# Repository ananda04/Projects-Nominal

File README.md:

# Projects-Nominal

A collection of applications, hardware designs, and automation tools built for the Nominal Connect ecosystem.

## Projects Overview

### `ciRACK`
Configurations, soft-control utilities, and automation scripts for managing hardware test rack infrastructure and VISA-connected instrumentation.

### `connectBAMBU`
Nominal Connect application for integrating Bambu Lab 3D printers, processing G-code print instructions, and streaming telemetry to Nominal.

### `connectModule`
Custom hardware design and embedded setup for a standalone RS-232 to Ethernet adapter board running Connect Engine to enable no-code test rack instrument interfacing.

### `gem5-connect`
Nominal Connect runner and data processing pipeline for executing gem5 Garnet Network-on-Chip (NoC) synthetic traffic sweeps via Docker and streaming post-evaluation telemetry to Nominal Core.

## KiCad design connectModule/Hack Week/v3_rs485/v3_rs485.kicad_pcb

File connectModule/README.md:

# Connect Serial-to-Ethernet Node

Standalone hardware adapter that bridges legacy test rack equipment (RS-232 / SCPI) to the Nominal Connect ecosystem via Ethernet. By running an embedded instance of Connect Engine directly on the node, it offloads driver execution and enables a no-code setup for test instrumentation.

## Implementation & Demo

The final implementation was scaled to run on a Raspberry Pi Compute platform running Linux. This preserved full Rust standard library (`std`) support, dynamic driver loading, and rapid SSH deployment without requiring a re-architecture of Connect Engine.

* Demo Video: https://youtu.be/hmSoeRTddCs?si=SxnHFOz03OIot3RP

## Key Hardware Specifications

* Power Input: 9–30V DC via 2-pin screw terminals (Buck converter rated up to 60V for potential future PoE support).
* Serial Interface: Male DB9 connector supporting RS-232 levels via MAX3232 transceiver.
* Network Interface: 100 Mbps RJ45 Ethernet using a W5500 SPI controller.
* Compute & Storage: Raspberry Pi Zero 2 W (Quad-core ARM Cortex-A53) with MicroSD for local OS and logging.

## Circuit Summary

* Power Subsystem: 9–30V DC input -> 4-60V Buck Converter (5V output) -> AMS1117-3.3 LDO (3.3V rail for level shifters and PHY).
* Serial Communication: DB9 RS-232 (+/-15V) converted to 3.3V logic via MAX3232 transceiver to Pi UART.
* Network Subsystem: W5500 IC offloads TCP/IP processing over SPI to the Pi, outputting via an integrated magnetics RJ45 jack.

## Software & Workflow

1. Stack: Raspberry Pi OS (Linux) running Connect Engine (compiled in Rust) integrated with Nominal Data Link for telemetry and commanding.
2. Setup: Connect DB9 to target instrument, attach Ethernet, and apply 9–30V DC power.
3. Usage: Locate node in Nominal Connect UI, configure instrument protocol, and control hardware without custom code.

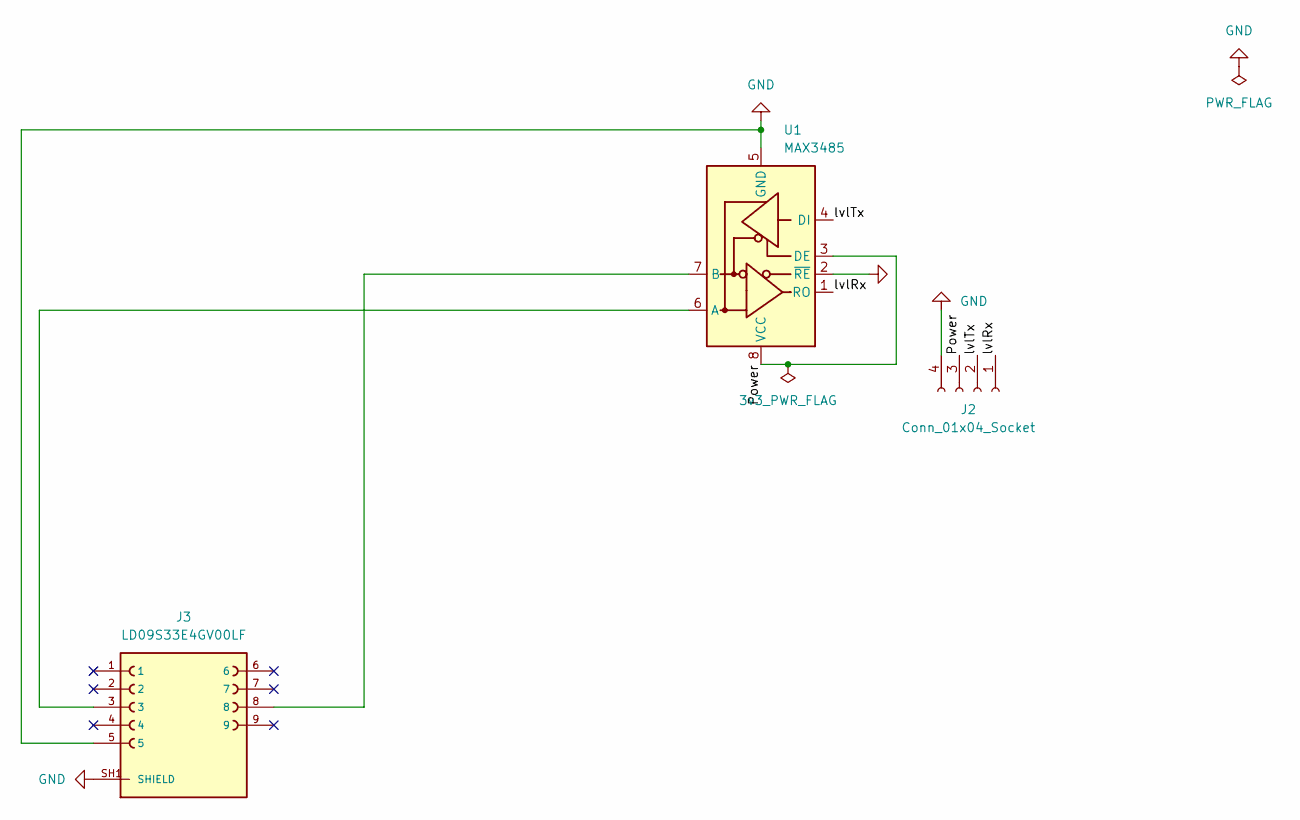
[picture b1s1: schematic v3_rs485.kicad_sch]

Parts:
J2: Conn_01x04_Socket; PinSocket_1x04_P2.54mm_Vertical
J3: LD09S33E4GV00LF; AMPHENOL_LD09S33E4GV00LF; PARTREV B
U1: MAX3485; SOIC-8_3.9x4.9mm_P1.27mm

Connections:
/Power: J2.3, U1.3 (DE), U1.8 (VCC)
/lvlRx: J2.1, U1.1 (RO)
/lvlTx: J2.2, U1.4 (DI)
GND: J2.4, J3.5, J3.SH1 (SHIELD), J3.SH2 (SHIELD), U1.2 (~RE), U1.5 (GND)
unnamed: J3.3, U1.6 (A)
unnamed: J3.8, U1.7 (B)

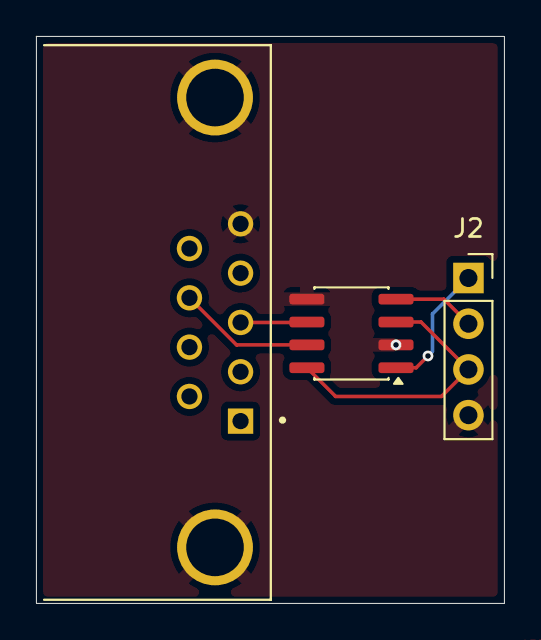
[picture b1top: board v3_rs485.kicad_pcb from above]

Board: 2 copper layers, 26.0 x 31.5 mm, 3 parts (0 on the bottom side), 6 nets.

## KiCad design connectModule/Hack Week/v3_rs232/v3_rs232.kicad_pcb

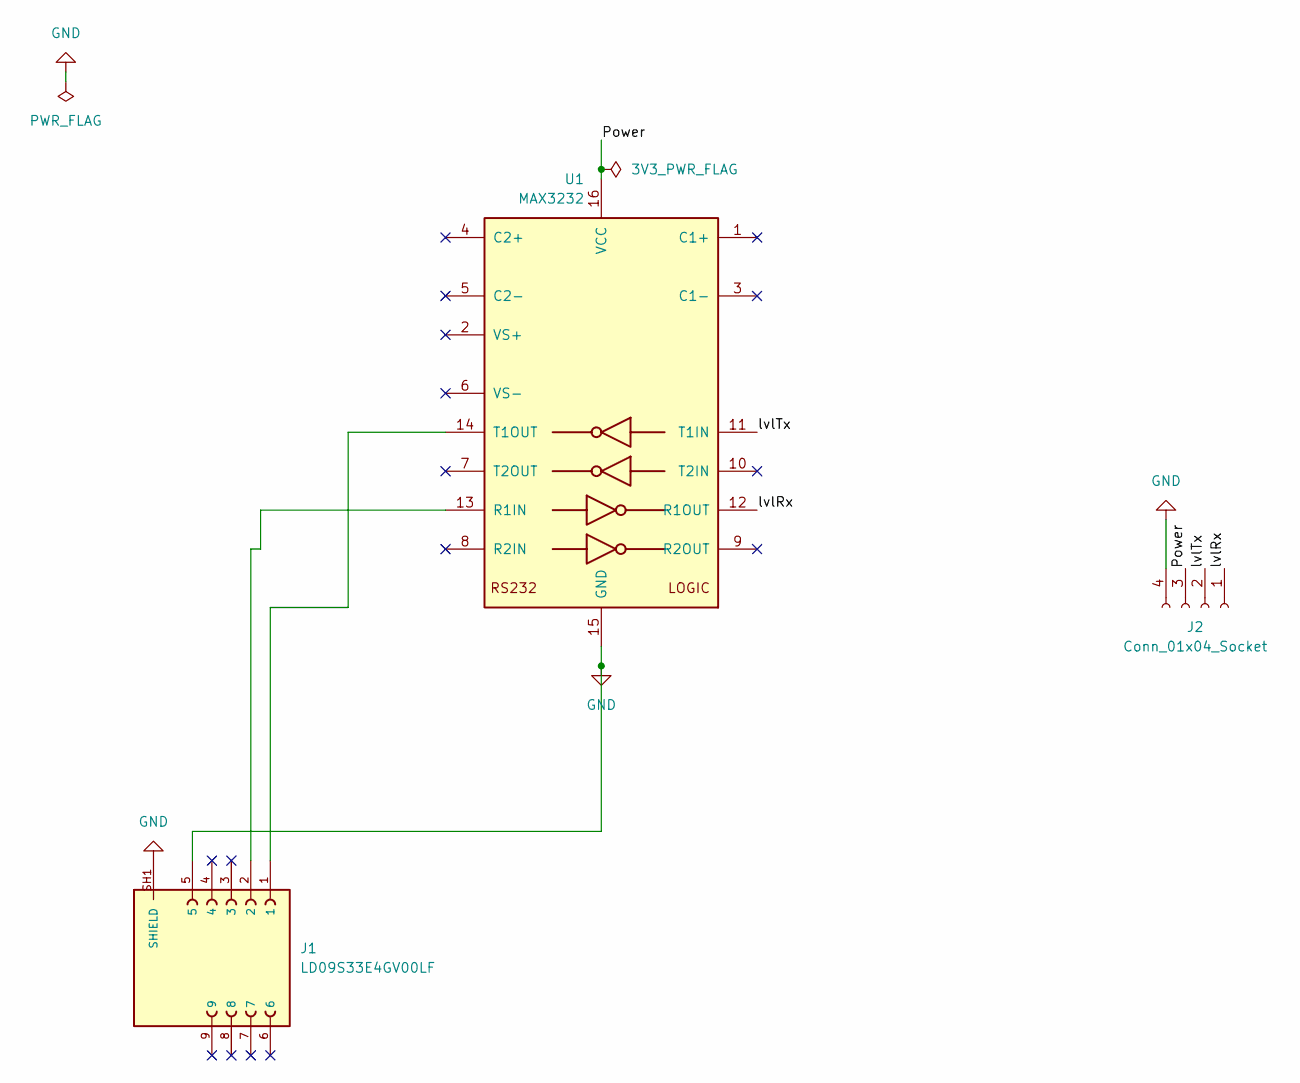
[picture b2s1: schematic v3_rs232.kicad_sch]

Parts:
J1: LD09S33E4GV00LF; AMPHENOL_LD09S33E4GV00LF; PARTREV B
J2: Conn_01x04_Socket; PinSocket_1x04_P2.54mm_Vertical
U1: MAX3232; TSSOP-16_4.4x5mm_P0.65mm

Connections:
/Power: J2.3, U1.16 (VCC)
/lvlRx: J2.1, U1.12 (R1OUT)
/lvlTx: J2.2, U1.11 (T1IN)
GND: J1.5, J1.SH1 (SHIELD), J1.SH2 (SHIELD), J2.4, U1.15 (GND)
unnamed: J1.2, U1.13 (R1IN)
unnamed: J1.1, U1.14 (T1OUT)

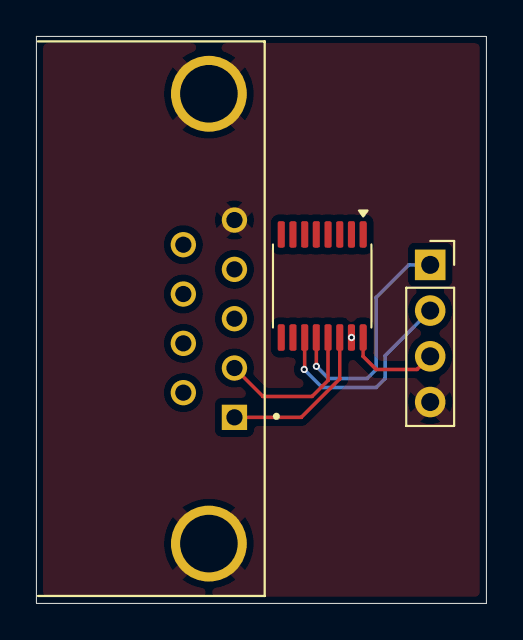
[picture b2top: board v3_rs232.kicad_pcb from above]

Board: 2 copper layers, 25.0 x 31.5 mm, 3 parts (0 on the bottom side), 6 nets.

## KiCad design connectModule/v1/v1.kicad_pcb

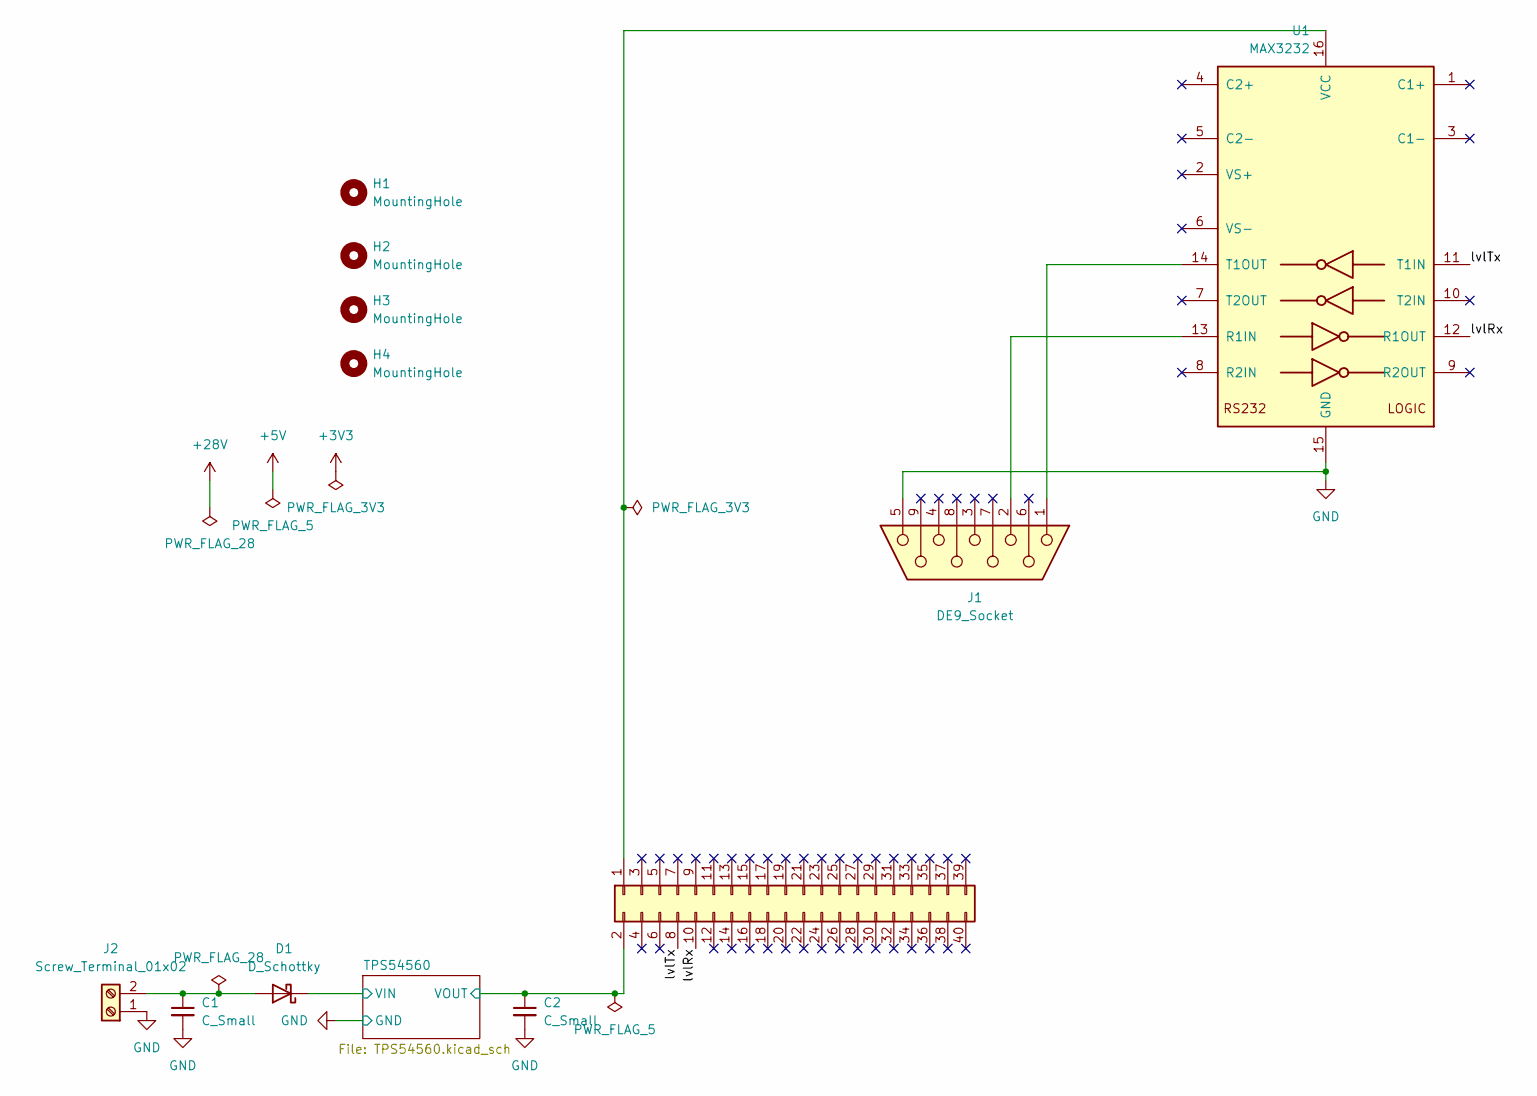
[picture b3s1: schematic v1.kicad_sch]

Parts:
C1, C2: C_Small; C_0402_1005Metric
D1: D_Schottky; D_SMB
H1, H2, H3, H4: MountingHole; MountingHole_2.7mm_M2.5
J1: DE9_Socket; DSUB-9_Socket_EdgeMount_P2.77mm
J2: Screw_Terminal_01x02; TerminalBlock_Phoenix_MKDS-1,5-2_1x02_P5.00mm_Horizontal
J7: Conn_02x20_Odd_Even; PinHeader_2x20_P2.54mm_Vertical
U1: MAX3232; TSSOP-16_4.4x5mm_P0.65mm

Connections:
/TPS54560/VIN: D1.1 (K); also elsewhere on the board
/TPS54560/VOUT: C2.1, J7.2; also elsewhere on the board
/lvlRx: J7.10, U1.12 (R1OUT)
/lvlTx: J7.8, U1.11 (T1IN)
GND: C1.2, C2.2, J1.5, J2.1, U1.15 (GND); also elsewhere on the board
unnamed: C1.1, D1.2 (A), J2.2
unnamed: J7.1, U1.16 (VCC)
unnamed: J1.2, U1.13 (R1IN)
unnamed: J1.1, U1.14 (T1OUT)

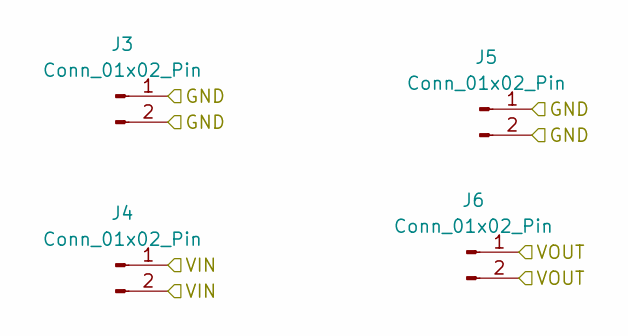
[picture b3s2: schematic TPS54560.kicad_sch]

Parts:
J3, J4, J5, J6: Conn_01x02_Pin; PinHeader_1x02_P2.54mm_Vertical

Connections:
/TPS54560/VIN: J4.1, J4.2; also elsewhere on the board
/TPS54560/VOUT: J6.1, J6.2; also elsewhere on the board
GND: J3.1, J3.2, J5.1, J5.2; also elsewhere on the board

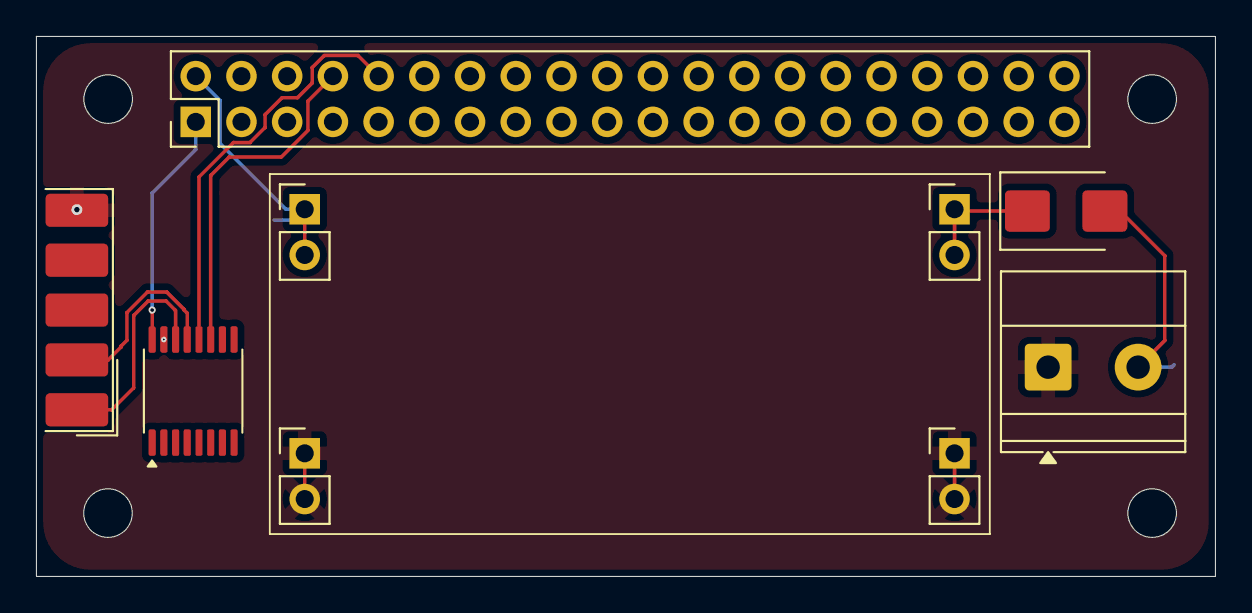
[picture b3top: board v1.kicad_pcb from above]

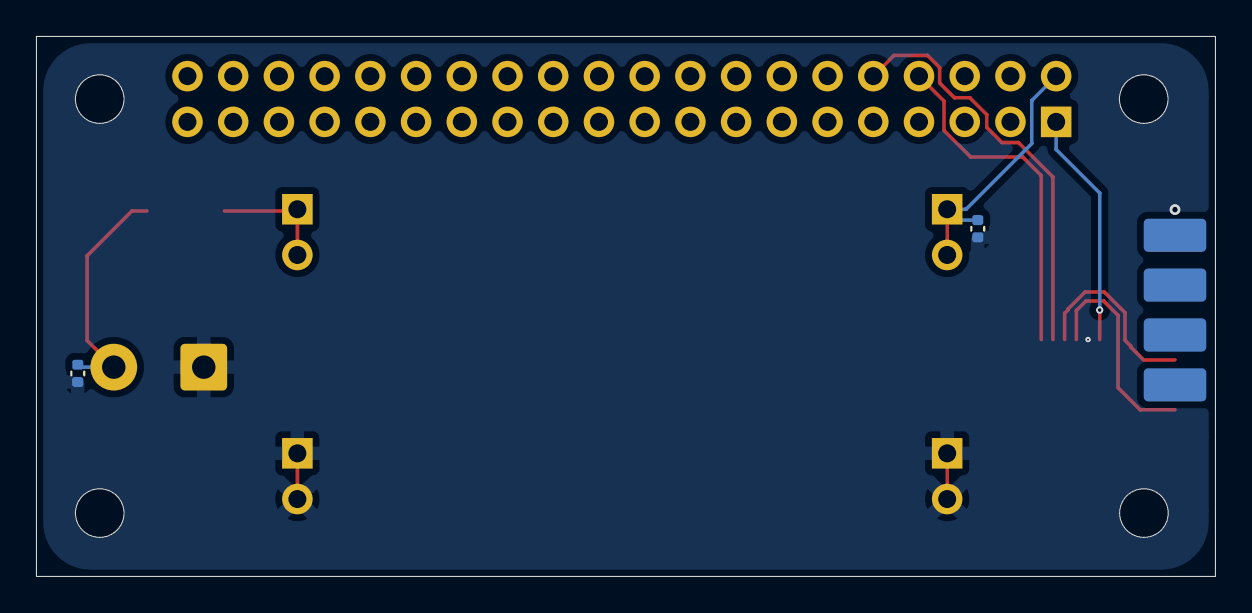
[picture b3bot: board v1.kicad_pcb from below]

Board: 2 copper layers, 65.5 x 30.0 mm, 15 parts (2 on the bottom side), 9 nets.

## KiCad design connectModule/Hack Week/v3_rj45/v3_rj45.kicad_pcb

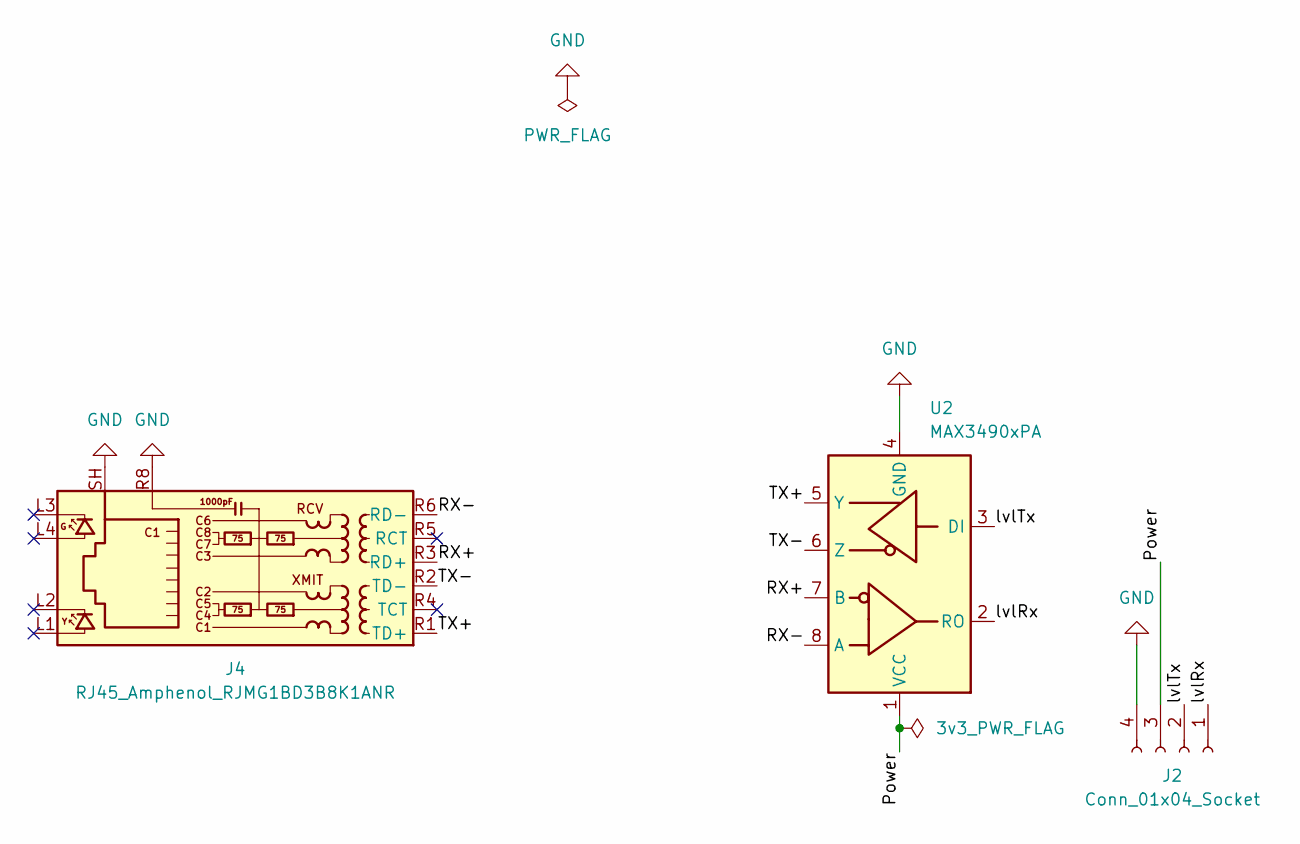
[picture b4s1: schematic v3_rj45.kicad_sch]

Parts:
J2: Conn_01x04_Socket; PinSocket_1x04_P2.54mm_Vertical
J4: RJ45_Amphenol_RJMG1BD3B8K1ANR
U2: MAX3490xPA; DIP-8_W7.62mm

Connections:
/Power: J2.3, U2.1 (VCC)
/RX+: J4.R3 (RD+), U2.7 (B)
/RX-: J4.R6 (RD-), U2.8 (A)
/TX+: J4.R1 (TD+), U2.5 (Y)
/TX-: J4.R2 (TD-), U2.6 (Z)
/lvlRx: J2.1, U2.2 (RO)
/lvlTx: J2.2, U2.3 (DI)
GND: J2.4, J4.R8, J4.SH, U2.4 (GND)

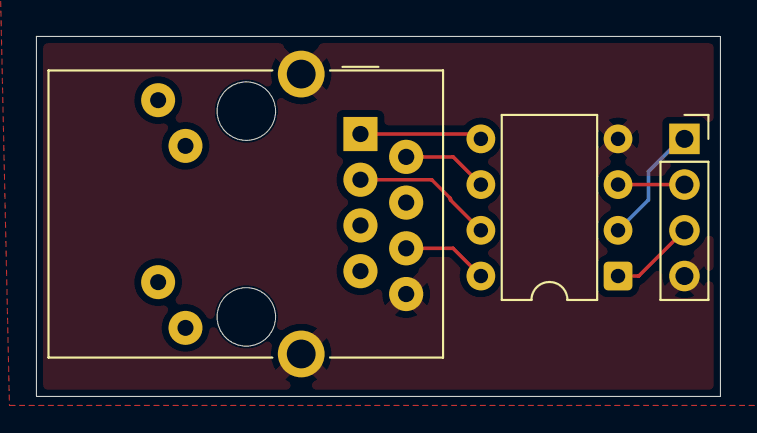
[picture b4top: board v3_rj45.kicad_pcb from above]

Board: 2 copper layers, 38.0 x 20.0 mm, 3 parts (0 on the bottom side), 8 nets.

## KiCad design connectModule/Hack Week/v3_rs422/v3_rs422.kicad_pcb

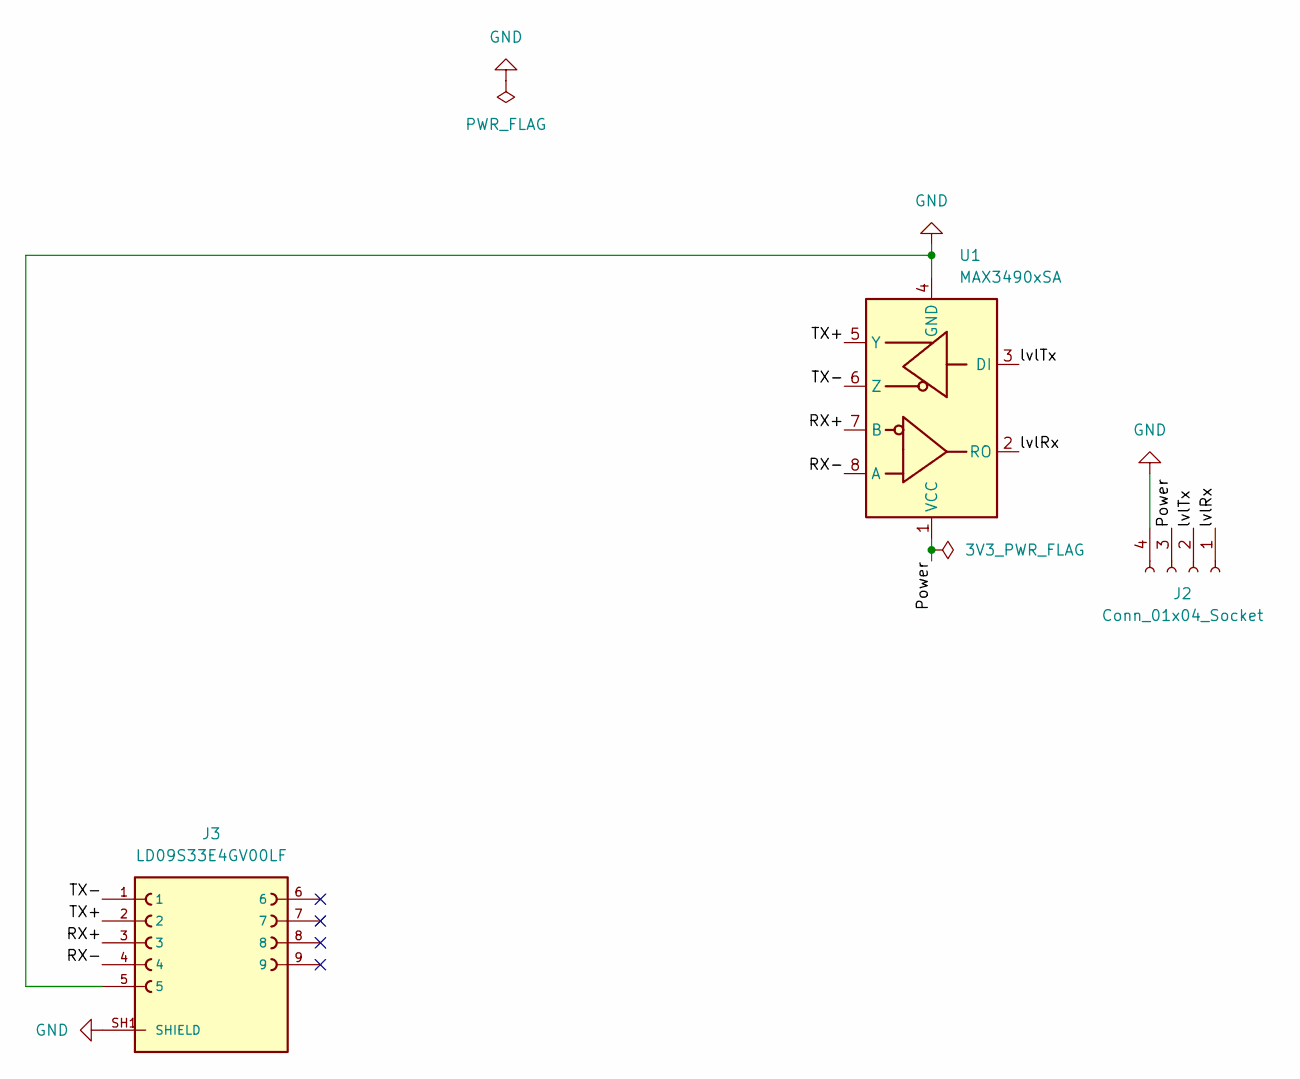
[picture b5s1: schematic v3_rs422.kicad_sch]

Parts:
J2: Conn_01x04_Socket; PinSocket_1x04_P2.54mm_Vertical
J3: LD09S33E4GV00LF; AMPHENOL_LD09S33E4GV00LF; PARTREV B
U1: MAX3490xSA; SOIC-8_3.9x4.9mm_P1.27mm

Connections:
/Power: J2.3, U1.1 (VCC)
/RX+: J3.3, U1.7 (B)
/RX-: J3.4, U1.8 (A)
/TX+: J3.2, U1.5 (Y)
/TX-: J3.1, U1.6 (Z)
/lvlRx: J2.1, U1.2 (RO)
/lvlTx: J2.2, U1.3 (DI)
GND: J2.4, J3.5, J3.SH1 (SHIELD), J3.SH2 (SHIELD), U1.4 (GND)

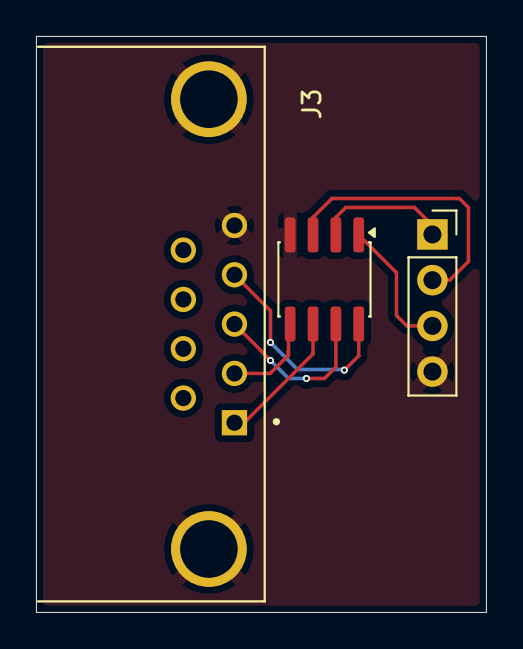
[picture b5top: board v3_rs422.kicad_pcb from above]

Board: 2 copper layers, 25.0 x 32.0 mm, 3 parts (0 on the bottom side), 8 nets.

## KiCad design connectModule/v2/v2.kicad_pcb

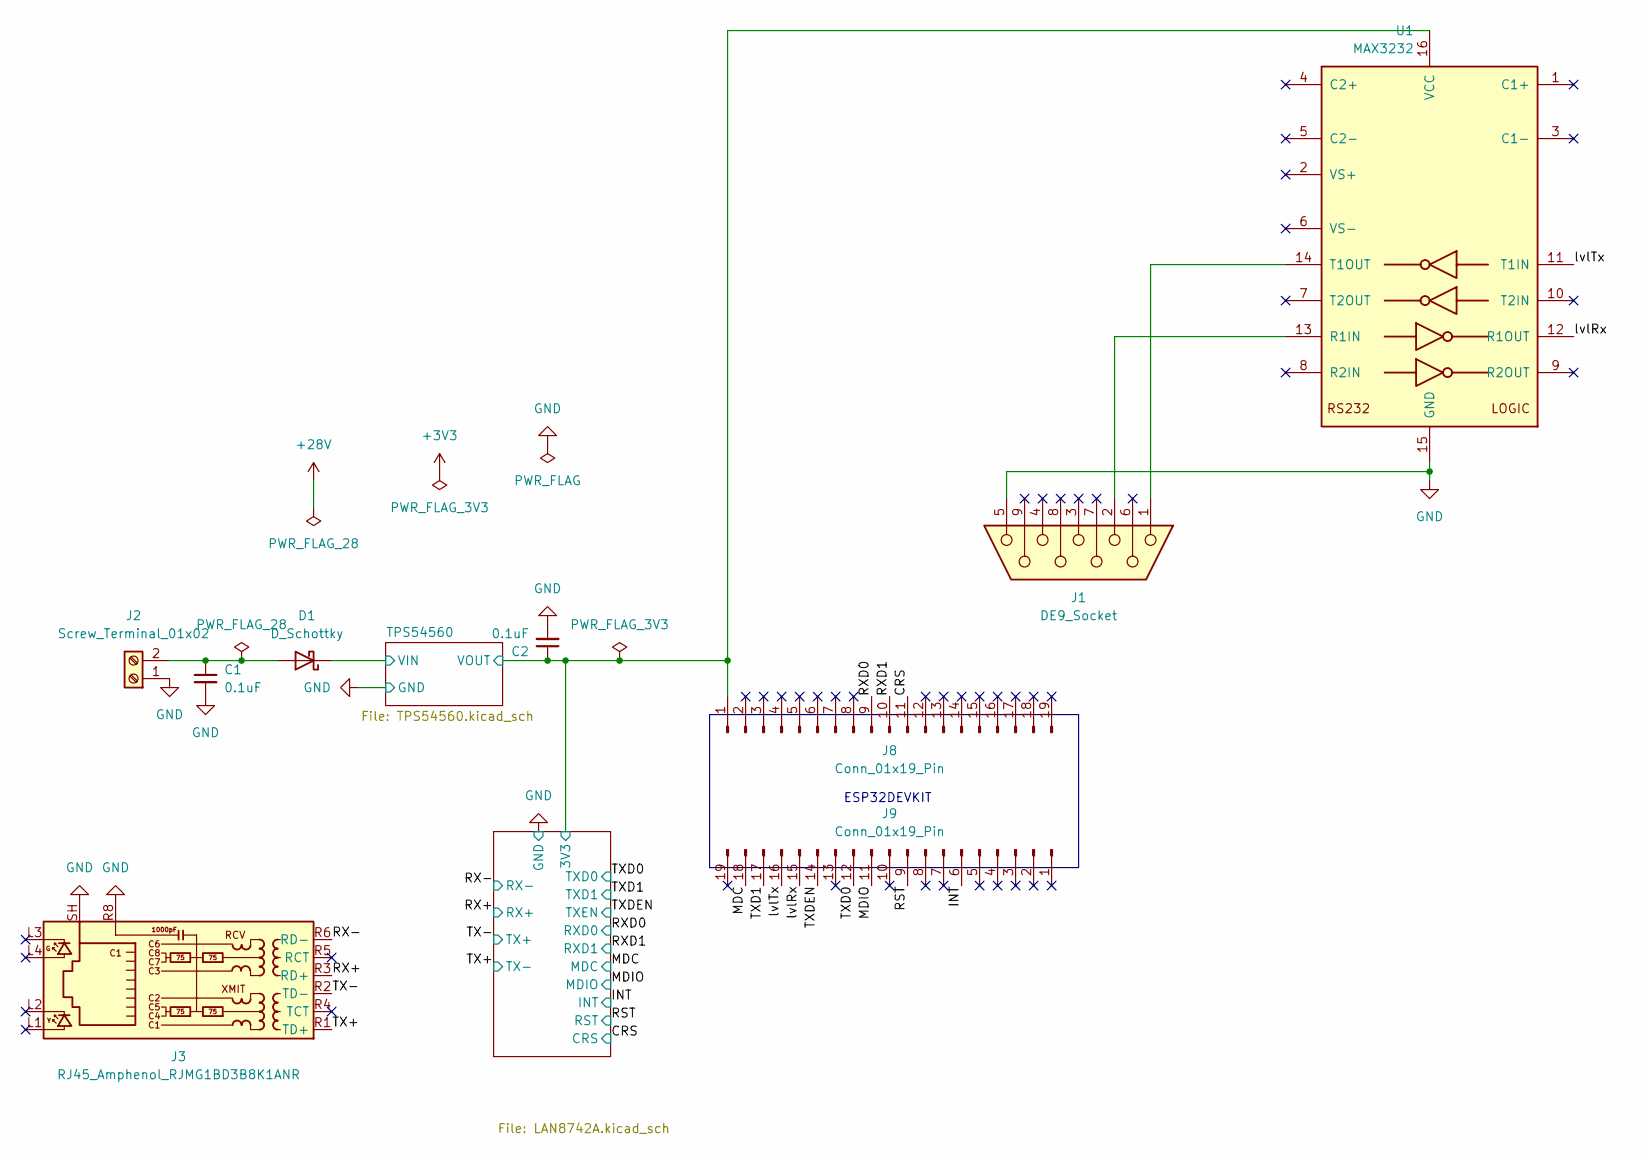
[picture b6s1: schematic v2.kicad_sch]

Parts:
C1, C2: 0.1uF; C_0402_1005Metric
D1: D_Schottky; D_SMB
J1: DE9_Socket; DSUB-9_Socket_EdgeMount_P2.77mm
J2: Screw_Terminal_01x02; TerminalBlock_Phoenix_MKDS-1,5-2_1x02_P5.00mm_Horizontal
J3: RJ45_Amphenol_RJMG1BD3B8K1ANR
J8, J9: Conn_01x19_Pin; PinSocket_1x19_P2.54mm_Vertical
U1: MAX3232; TSSOP-16_4.4x5mm_P0.65mm

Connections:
/CRS: J8.11; also elsewhere on the board
/INT: J9.6; also elsewhere on the board
/LAN8742A/3V3: C2.1, J8.1, U1.16 (VCC); also elsewhere on the board
/MDC: J9.18; also elsewhere on the board
/MDIO: J9.11; also elsewhere on the board
/RST: J9.9; also elsewhere on the board
/RX+: J3.R3 (RD+); also elsewhere on the board
/RX-: J3.R6 (RD-); also elsewhere on the board
/RXD0: J8.9; also elsewhere on the board
/RXD1: J8.10; also elsewhere on the board
/TPS54560/VIN: D1.1 (K); also elsewhere on the board
/TX+: J3.R1 (TD+); also elsewhere on the board
/TX-: J3.R2 (TD-); also elsewhere on the board
/TXD0: J9.12; also elsewhere on the board
/TXD1: J9.17; also elsewhere on the board
/TXDEN: J9.14; also elsewhere on the board
/lvlRx: J9.15, U1.12 (R1OUT)
/lvlTx: J9.16, U1.11 (T1IN)
GND: C1.2, C2.2, J1.5, J2.1, J3.R8, J3.SH, U1.15 (GND); also elsewhere on the board
unnamed: C1.1, D1.2 (A), J2.2
unnamed: J1.2, U1.13 (R1IN)
unnamed: J1.1, U1.14 (T1OUT)

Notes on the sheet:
ESP32DEVKIT

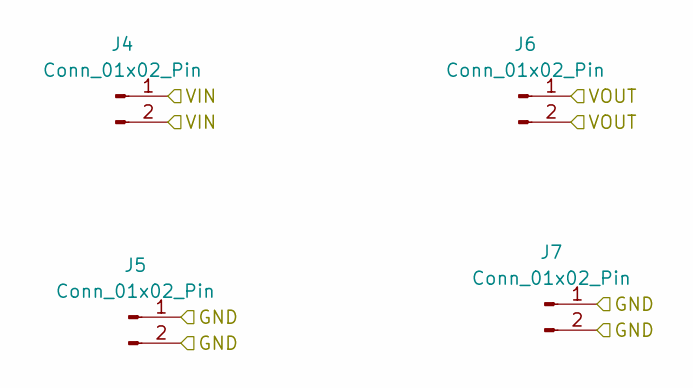
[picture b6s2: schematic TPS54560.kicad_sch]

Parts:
J4, J5, J6, J7: Conn_01x02_Pin; PinHeader_1x02_P2.54mm_Vertical

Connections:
/LAN8742A/3V3: J6.1, J6.2; also elsewhere on the board
/TPS54560/VIN: J4.1, J4.2; also elsewhere on the board
GND: J5.1, J5.2, J7.1, J7.2; also elsewhere on the board

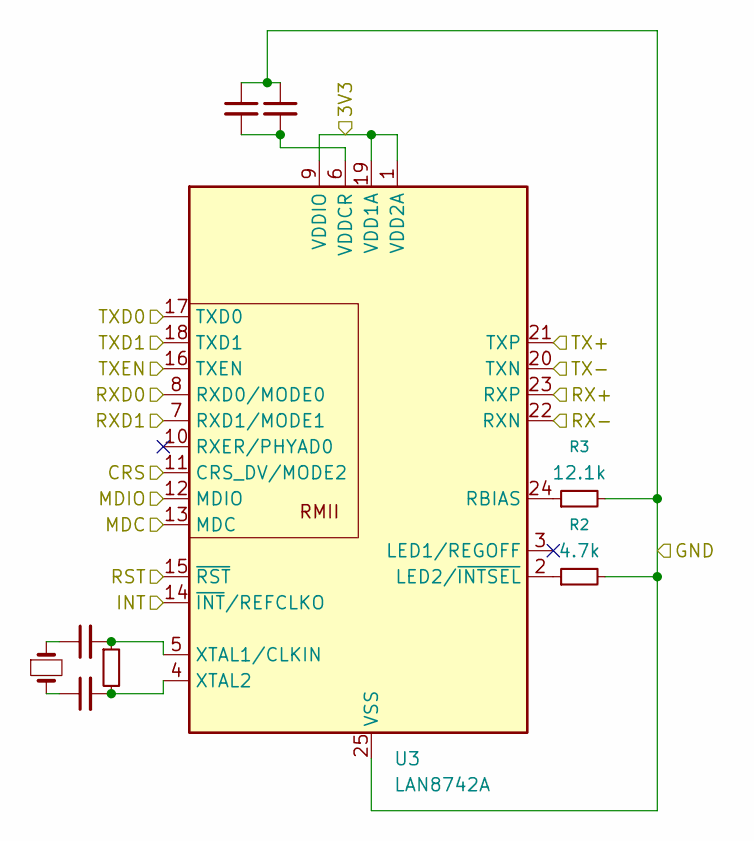
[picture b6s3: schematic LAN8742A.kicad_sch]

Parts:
C3, C4: 22pF; C_0402_1005Metric
C5: 1uF; C_0603_1608Metric
C6: 470pF; C_0402_1005Metric
R1: 1M; R_0402_1005Metric
R2: 4.7k; R_0402_1005Metric
R3: 12.1k; R_0402_1005Metric
U3: LAN8742A; VQFN-24-1EP_4x4mm_P0.5mm_EP2.5x2.5mm_ThermalVias
Y1: Crystal_Small; Crystal_SMD_3225-4Pin_3.2x2.5mm

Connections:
/CRS: U3.11 (CRS_DV/MODE2); also elsewhere on the board
/INT: U3.14 (~INT/REFCLKO); also elsewhere on the board
/LAN8742A/3V3: U3.1 (VDD2A), U3.9 (VDDIO), U3.19 (VDD1A); also elsewhere on the board
/MDC: U3.13 (MDC); also elsewhere on the board
/MDIO: U3.12 (MDIO); also elsewhere on the board
/RST: U3.15 (~RST); also elsewhere on the board
/RX+: U3.23 (RXP); also elsewhere on the board
/RX-: U3.22 (RXN); also elsewhere on the board
/RXD0: U3.8 (RXD0/MODE0); also elsewhere on the board
/RXD1: U3.7 (RXD1/MODE1); also elsewhere on the board
/TX+: U3.20 (TXN); also elsewhere on the board
/TX-: U3.21 (TXP); also elsewhere on the board
/TXD0: U3.17 (TXD0); also elsewhere on the board
/TXD1: U3.18 (TXD1); also elsewhere on the board
/TXDEN: U3.16 (TXEN); also elsewhere on the board
GND: C5.1, C6.1, R2.2, R3.2, U3.25 (VSS); also elsewhere on the board
unnamed: C3.1, Y1.1
unnamed: C4.1, Y1.2
unnamed: R2.1, U3.2 (LED2/~INTSEL)
unnamed: R3.1, U3.24 (RBIAS)
unnamed: C5.2, C6.2, U3.6 (VDDCR)
unnamed: C3.2, R1.1, U3.5 (XTAL1/CLKIN)
unnamed: C4.2, R1.2, U3.4 (XTAL2)

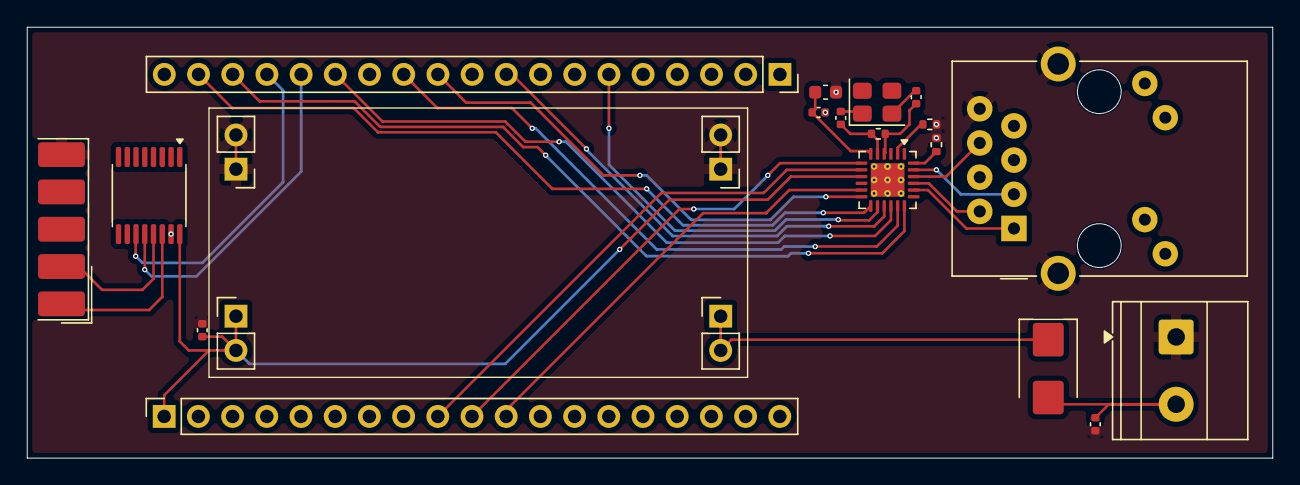
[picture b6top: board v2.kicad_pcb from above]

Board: 2 copper layers, 92.5 x 32.0 mm, 22 parts (0 on the bottom side), 29 nets.

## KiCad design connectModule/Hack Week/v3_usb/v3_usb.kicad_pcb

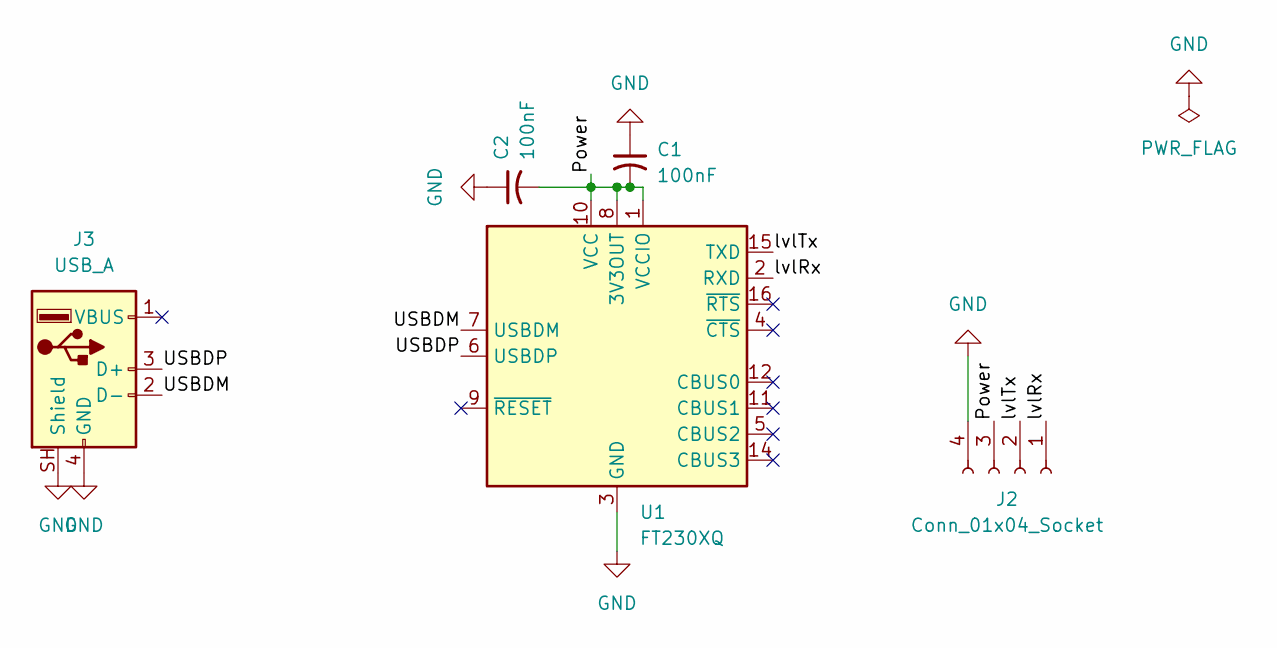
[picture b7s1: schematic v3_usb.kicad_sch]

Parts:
C1, C2: 100nF; C_0603_1608Metric
J2: Conn_01x04_Socket; PinSocket_1x04_P2.54mm_Vertical
J3: USB_A; USB_A_Wuerth_614004134726_Horizontal
U1: FT230XQ; QFN-16-1EP_4x4mm_P0.65mm_EP2.1x2.1mm

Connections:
/Power: C1.2, C2.2, J2.3, U1.1 (VCCIO), U1.8 (3V3OUT), U1.10 (VCC)
/USBDM: J3.2 (D-), U1.7 (USBDM)
/USBDP: J3.3 (D+), U1.6 (USBDP)
/lvlRx: J2.1, U1.2 (RXD)
/lvlTx: J2.2, U1.15 (TXD)
GND: C1.1, C2.1, J2.4, J3.4 (GND), J3.SH (Shield), U1.3 (GND), U1.13 (GND), U1.17 (GND)

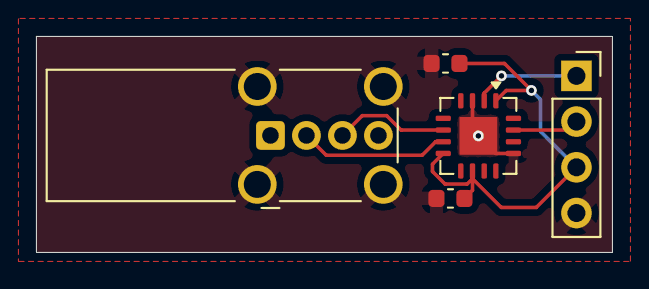
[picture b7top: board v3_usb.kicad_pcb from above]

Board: 2 copper layers, 32.0 x 12.0 mm, 5 parts (0 on the bottom side), 6 nets.
